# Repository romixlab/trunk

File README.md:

trunk
=====
Just some projects of mine

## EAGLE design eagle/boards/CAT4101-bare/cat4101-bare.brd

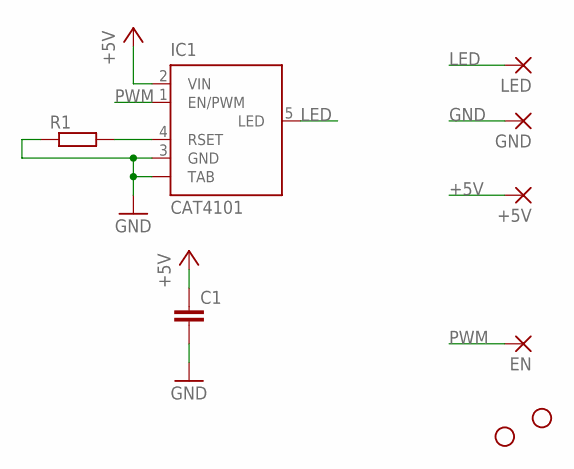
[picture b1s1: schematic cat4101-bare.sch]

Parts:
+5V: SMD2; SMD1,27-2,54
C1: C-EUC0805K; C0805K
EN: SMD2; SMD1,27-2,54
GND: SMD5; SMD2,54-5,08
IC1: CAT4101; TO263_5
JP1, JP2: STAND-OFF
LED: SMD5; SMD2,54-5,08
R1: R-EU_R0805; R0805

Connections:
+5V: +5V.1, C1.1, IC1.2 (VIN)
GND: C1.2, GND.1, IC1.3 (GND), IC1.TAB, R1.1
LED: IC1.5 (LED), LED.1
unnamed: IC1.4 (RSET), R1.2
PWM: EN.1, IC1.1 (EN/PWM)

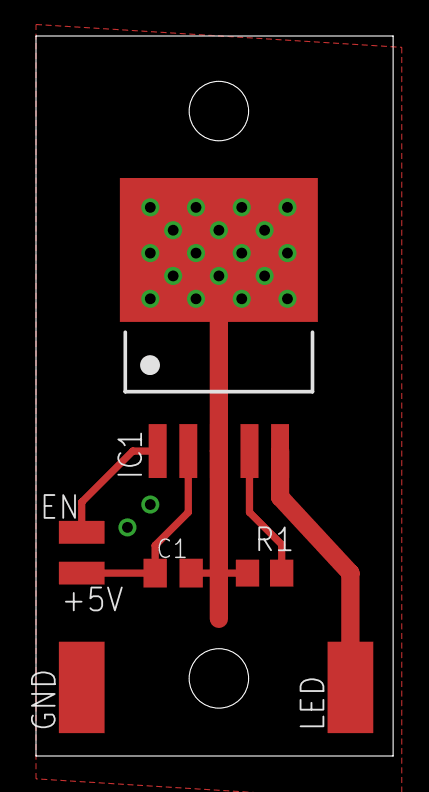
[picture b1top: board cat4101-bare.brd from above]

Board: 2 copper layers, 19.8 x 40.0 mm, 9 parts (0 on the bottom side), 5 nets.

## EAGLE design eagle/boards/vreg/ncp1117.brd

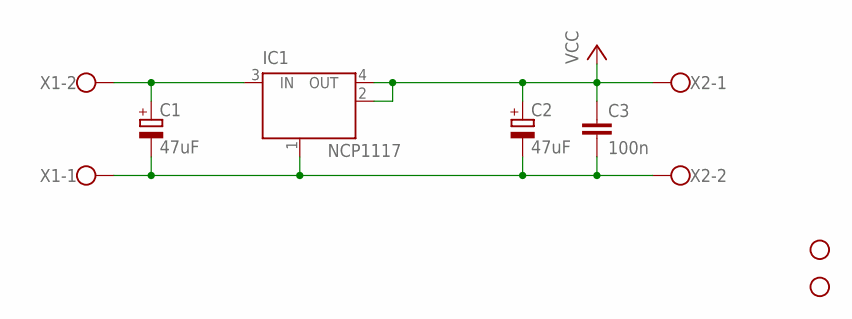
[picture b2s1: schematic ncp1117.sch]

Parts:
C1, C2: 47uF; E2,5-5
C3: 100n; C1206K
IC1: NCP1117; SOT223
STANDOFF1, STANDOFF2: STAND-OFF
X1, X2: W237-102

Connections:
unnamed: C1.+, IC1.3 (IN), X1.2
unnamed: C1.-, C2.-, C3.2, IC1.1 (GND/ADJ), X1.1, X2.2
VCC: C2.+, C3.1, IC1.2 (OUT), IC1.4 (OUT), X2.1

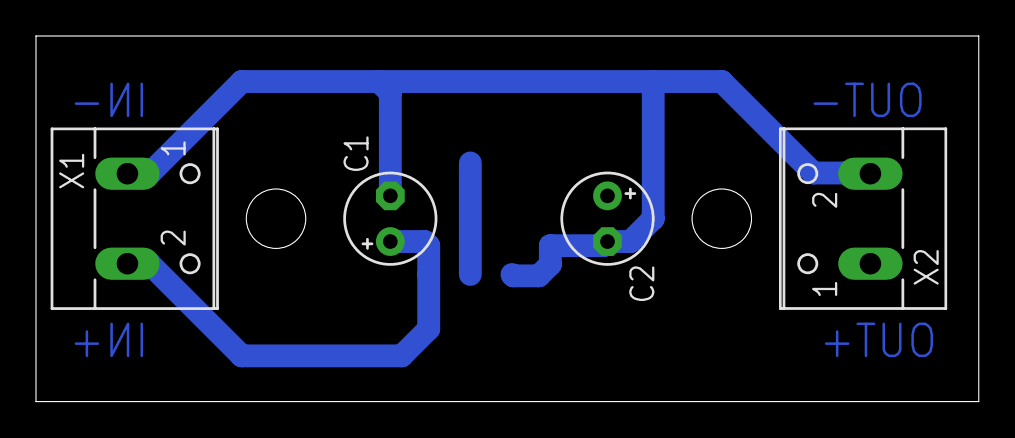
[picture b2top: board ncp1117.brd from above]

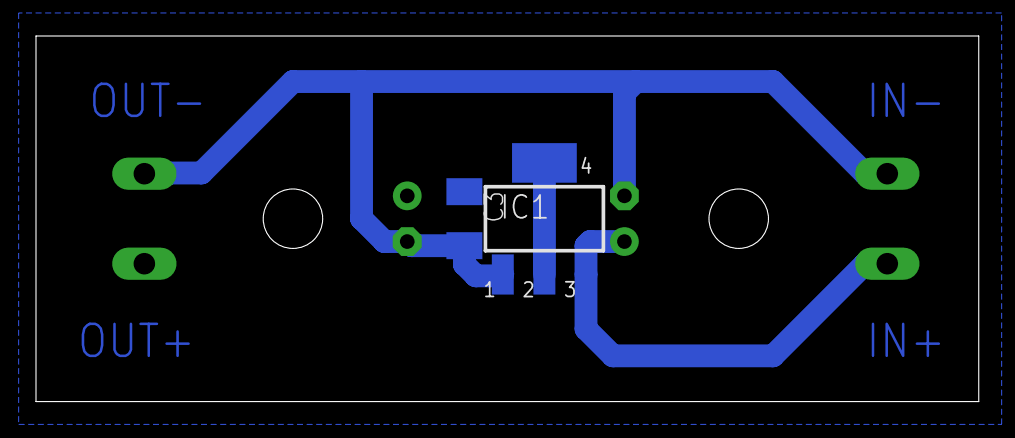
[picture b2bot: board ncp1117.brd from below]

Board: 2 copper layers, 52.4 x 20.3 mm, 8 parts (2 on the bottom side), 3 nets.

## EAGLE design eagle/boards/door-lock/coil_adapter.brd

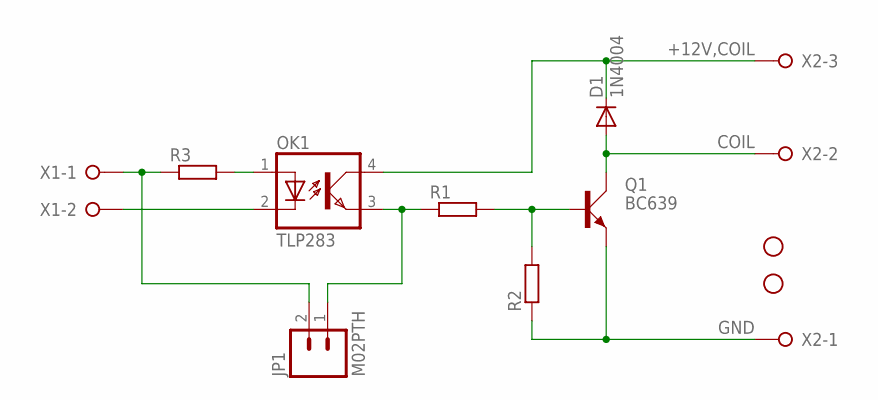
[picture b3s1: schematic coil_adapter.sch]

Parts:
D1: 1N4004; DO41-10
JP1: M02PTH; 1X02
OK1: TLP283; MINI-FLAT-4
Q1: BC639; SOT54D
R1, R2, R3: R-EU_R1206; R1206
STANDOFF1, STANDOFF2: STAND-OFF
X1: W237-02P; W237-132
X2: W237-03P; W237-133

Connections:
+12V,COIL: D1.C, OK1.4 (COL), X2.3
COIL: D1.A, Q1.C, X2.2
GND: Q1.E, R2.1, X2.1
unnamed: Q1.B, R1.2, R2.2
unnamed: JP1.1, OK1.3 (EMIT), R1.1
unnamed: JP1.2, R3.1, X1.1
unnamed: OK1.1 (A), R3.2
unnamed: OK1.2 (C), X1.2

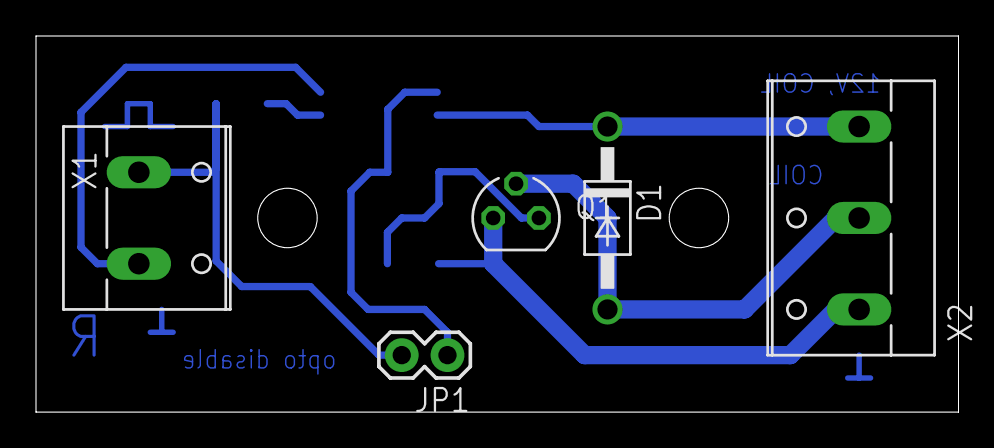
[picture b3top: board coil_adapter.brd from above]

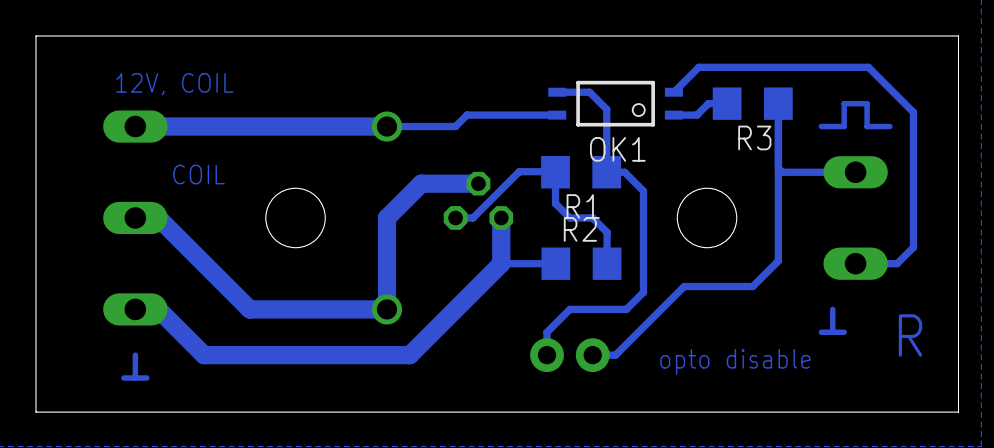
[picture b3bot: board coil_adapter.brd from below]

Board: 2 copper layers, 51.2 x 20.9 mm, 11 parts (4 on the bottom side), 8 nets.

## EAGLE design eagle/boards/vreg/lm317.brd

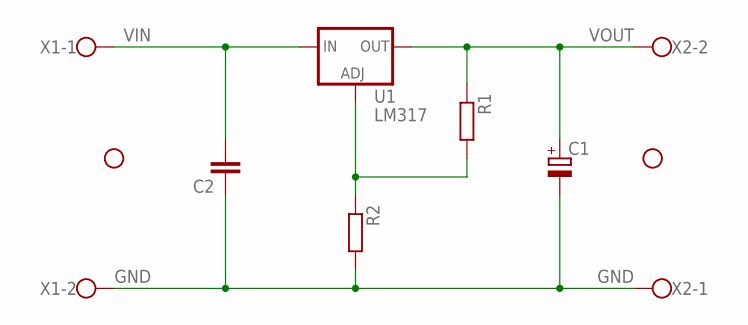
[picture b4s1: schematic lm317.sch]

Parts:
C1: CPOL-EUE2.5-6; E2,5-6
C2: C-EUC1206K; C1206K
R1, R2: R-EU_M1206; M1206
STANDOFF1, STANDOFF2: STAND-OFF
U1: LM317; TO220-ADJ
X1, X2: W237-102

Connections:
GND: C1.-, C2.1, R2.2, X1.2, X2.1
unnamed: R1.2, R2.1, U1.ADJ
VIN: C2.2, U1.IN, X1.1
VOUT: C1.+, R1.1, U1.OUT, X2.2

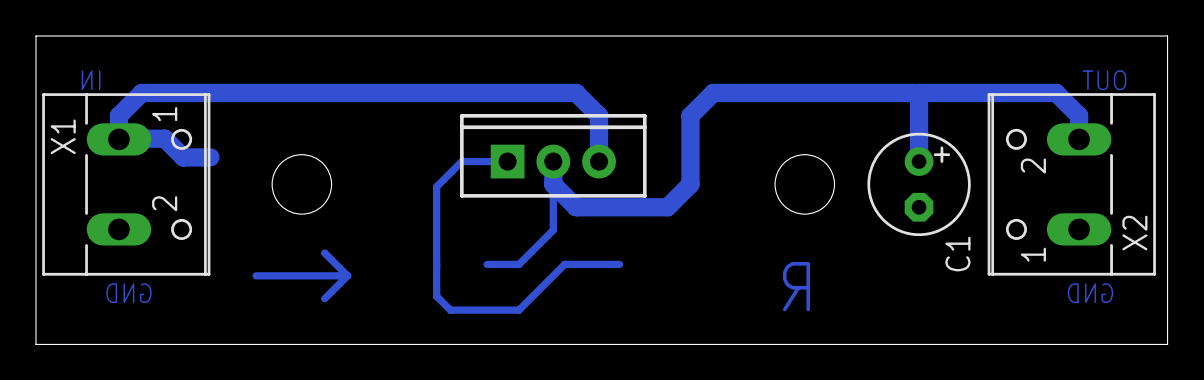
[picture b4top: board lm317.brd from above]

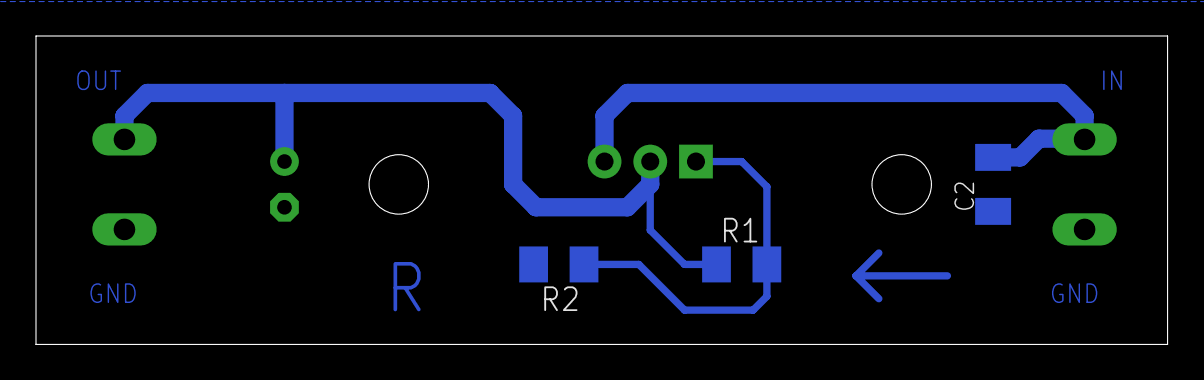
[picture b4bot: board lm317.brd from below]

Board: 2 copper layers, 62.9 x 17.1 mm, 9 parts (3 on the bottom side), 4 nets.

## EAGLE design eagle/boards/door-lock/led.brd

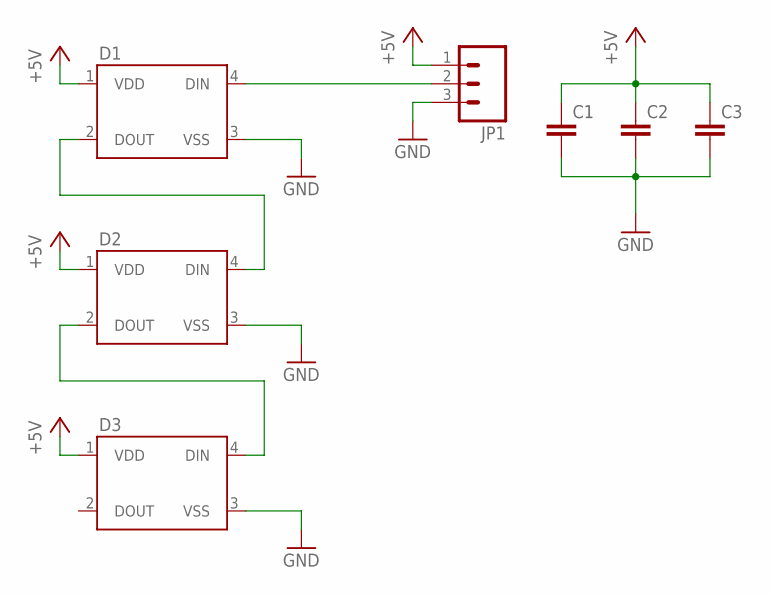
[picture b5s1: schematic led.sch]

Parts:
C1, C2, C3: CAP1206; 1206
D1, D2, D3: WS2812B
JP1: M03PTH; 1X03

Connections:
+5V: C1.1, C2.1, C3.1, D1.1 (VDD), D2.1 (VDD), D3.1 (VDD), JP1.1
GND: C1.2, C2.2, C3.2, D1.3 (VSS), D2.3 (VSS), D3.3 (VSS), JP1.3
unnamed: D1.2 (DOUT), D2.4 (DIN)
unnamed: D2.2 (DOUT), D3.4 (DIN)
unnamed: D1.4 (DIN), JP1.2

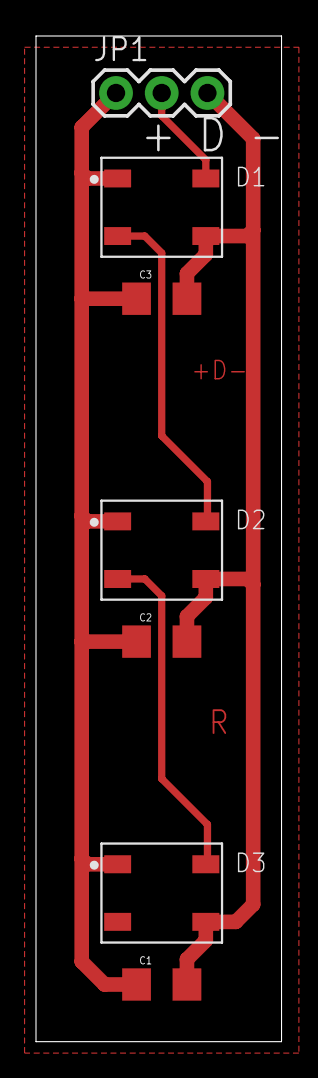
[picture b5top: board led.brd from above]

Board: 2 copper layers, 13.6 x 55.9 mm, 7 parts (0 on the bottom side), 5 nets.

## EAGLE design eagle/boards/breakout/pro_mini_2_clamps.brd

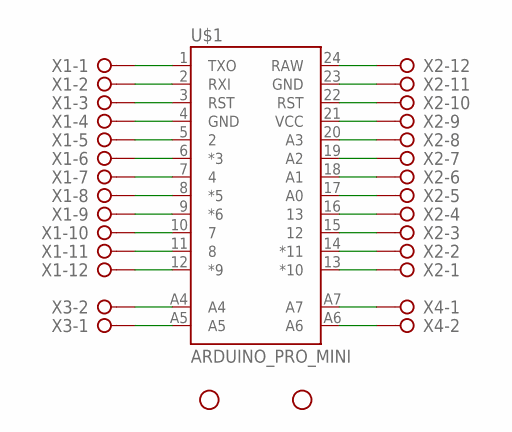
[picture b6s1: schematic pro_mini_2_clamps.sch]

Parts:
STANDOFF1, STANDOFF2: STAND-OFF
U$1: ARDUINO_PRO_MINI
X1, X2: W237-12P
X3, X4: W237-02P; W237-132

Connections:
unnamed: U$1.1 (TXO), X1.1
unnamed: U$1.2 (RXI), X1.2
unnamed: U$1.3 (RST), X1.3
unnamed: U$1.4 (GND), X1.4
unnamed: U$1.5 (2), X1.5
unnamed: U$1.6 (*3), X1.6
unnamed: U$1.7 (4), X1.7
unnamed: U$1.8 (*5), X1.8
unnamed: U$1.9 (*6), X1.9
unnamed: U$1.10 (7), X1.10
unnamed: U$1.11 (8), X1.11
unnamed: U$1.12 (*9), X1.12
unnamed: U$1.24 (RAW), X2.12
unnamed: U$1.23 (GND), X2.11
unnamed: U$1.22 (RST), X2.10
unnamed: U$1.21 (VCC), X2.9
unnamed: U$1.20 (A3), X2.8
unnamed: U$1.19 (A2), X2.7
unnamed: U$1.18 (A1), X2.6
unnamed: U$1.17 (A0), X2.5
unnamed: U$1.16 (13), X2.4
unnamed: U$1.15 (12), X2.3
unnamed: U$1.14 (*11), X2.2
unnamed: U$1.13 (*10), X2.1
unnamed: U$1.A7, X4.1
unnamed: U$1.A6, X4.2
unnamed: U$1.A4, X3.2
unnamed: U$1.A5, X3.1

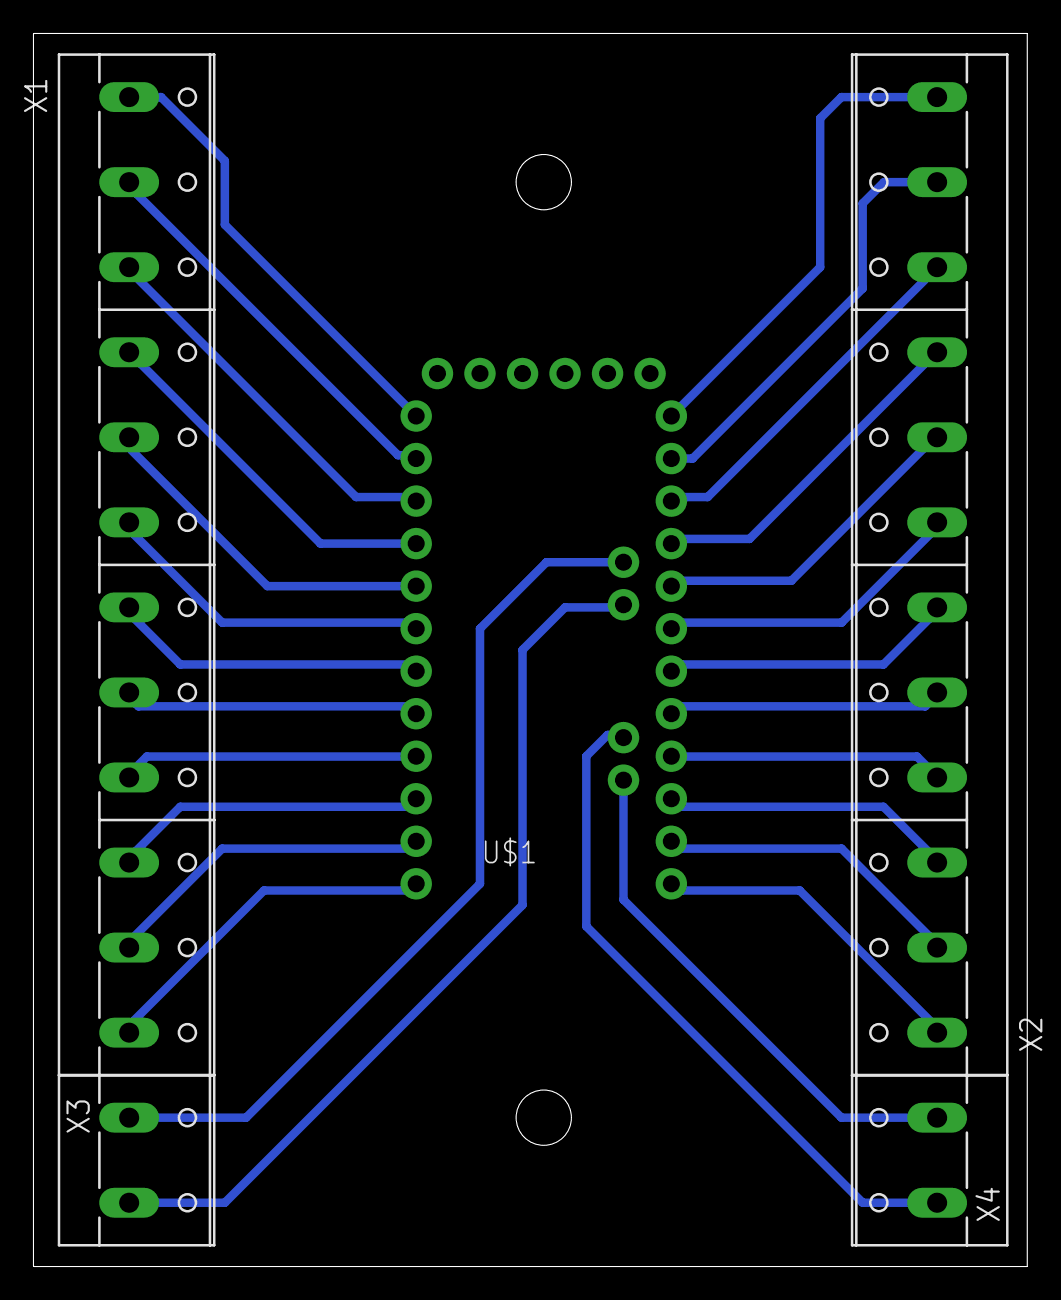
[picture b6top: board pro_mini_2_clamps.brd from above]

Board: 2 copper layers, 59.4 x 73.6 mm, 7 parts (0 on the bottom side), 28 nets.

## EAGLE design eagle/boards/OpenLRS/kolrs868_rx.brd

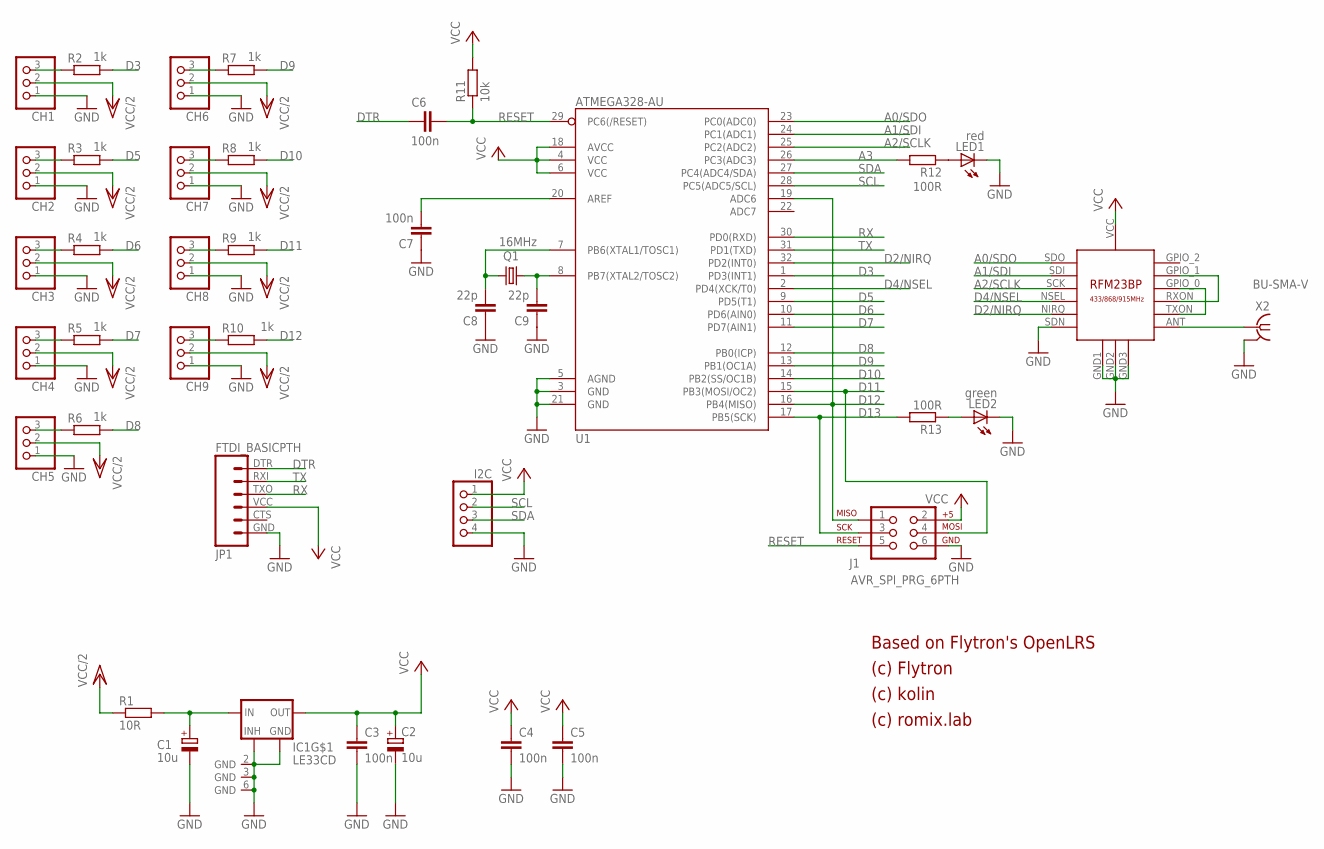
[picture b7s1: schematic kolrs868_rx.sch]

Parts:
C1, C2: 10u; SMC_B
C3, C4, C5, C6, C7: 100n; M0805
C8, C9: 22p; M0805
CH1, CH2, CH3, CH4, CH5, CH6, CH7, CH8, CH9: PINHD-1X3_KOLINOVO; 1X03
I2C: PINHD-1X4; 1X04
IC1: LE33CD; SO8
J1: AVR_SPI_PRG_6PTH; 2X3
JP1: FTDI_BASICPTH; FTDI_BASIC
LED1: red; CHIPLED_0805
LED2: green; CHIPLED_0805
Q1: 16MHz; HC49UP
R1: 10R; M0805
R2, R3, R4, R5, R6, R7, R8, R9, R10: 1k; M0805
R11: 10k; M0805
R12, R13: 100R; M0805
U1: ATMEGA328-AU; TQFP32-08
U$1: RFM23BP
X2: BU-SMA-V

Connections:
A0/SDO: U1.23 (PC0(ADC0)), U$1.SDO
A1/SDI: U1.24 (PC1(ADC1)), U$1.SDI
A2/SCLK: U1.25 (PC2(ADC2)), U$1.SCK
A3: R12.2, U1.26 (PC3(ADC3))
D2/NIRQ: U1.32 (PD2(INT0)), U$1.NIRQ
D3: R2.2, U1.1 (PD3(INT1))
D4/NSEL: U1.2 (PD4(XCK/T0)), U$1.NSEL
D5: R3.2, U1.9 (PD5(T1))
D6: R4.2, U1.10 (PD6(AIN0))
D7: R5.2, U1.11 (PD7(AIN1))
D8: R6.2, U1.12 (PB0(ICP))
D9: R7.2, U1.13 (PB1(OC1A))
D10: R8.2, U1.14 (PB2(SS/OC1B))
D11: J1.4, R9.2, U1.15 (PB3(MOSI/OC2))
D12: J1.1, R10.2, U1.16 (PB4(MISO)), U1.19 (ADC6)
D13: J1.3, R13.2, U1.17 (PB5(SCK))
DTR: C6.1, JP1.DTR (1)
GND: C1.-, C2.-, C3.2, C4.2, C5.2, C7.1, C8.1, C9.1, CH1.1, CH2.1, CH3.1, CH4.1, CH5.1, CH6.1, CH7.1, CH8.1, CH9.1, I2C.4, IC1.2 (GND), IC1.3 (GND), IC1.5 (INHIBIT), IC1.6 (GND), IC1.7 (GND), J1.6, JP1.GND (6), LED1.C, LED2.C, U1.3 (GND), U1.5 (AGND), U1.21 (GND), U$1.GND1, U$1.GND2, U$1.GND3, U$1.SDN, X2.2 (GND), X2.3 (GND), X2.4 (GND), X2.5 (GND)
unnamed: C7.2, U1.20 (AREF)
unnamed: U$1.ANT, X2.1
unnamed: LED1.A, R12.1
unnamed: C8.2, Q1.2, U1.7 (PB6(XTAL1/TOSC1))
unnamed: C9.2, Q1.1, U1.8 (PB7(XTAL2/TOSC2))
unnamed: C1.+, IC1.8 (IN), R1.2
unnamed: CH5.3, R6.1
unnamed: CH1.3, R2.1
unnamed: CH2.3, R3.1
unnamed: CH3.3, R4.1
unnamed: CH4.3, R5.1
unnamed: CH6.3, R7.1
unnamed: CH7.3, R8.1
unnamed: CH8.3, R9.1
unnamed: CH9.3, R10.1
unnamed: U$1.GPIO_0, U$1.TXON
unnamed: U$1.GPIO_1, U$1.RXON
unnamed: LED2.A, R13.1
RESET: C6.2, J1.5, R11.1, U1.29 (PC6(/RESET))
RX: JP1.TXO (3), U1.30 (PD0(RXD))
SCL: I2C.2, U1.28 (PC5(ADC5/SCL))
SDA: I2C.3, U1.27 (PC4(ADC4/SDA))
TX: JP1.RXI (2), U1.31 (PD1(TXD))
VCC: C2.+, C3.1, C4.1, C5.1, I2C.1, IC1.1 (OUT), J1.2, JP1.VCC (4), R11.2, U1.4 (VCC), U1.6 (VCC), U1.18 (AVCC), U$1.VCC
VCC/2: CH1.2, CH2.2, CH3.2, CH4.2, CH5.2, CH6.2, CH7.2, CH8.2, CH9.2, R1.1

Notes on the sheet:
Based on Flytron's OpenLRS
(c) Flytron
(c) kolin
(c) romix.lab

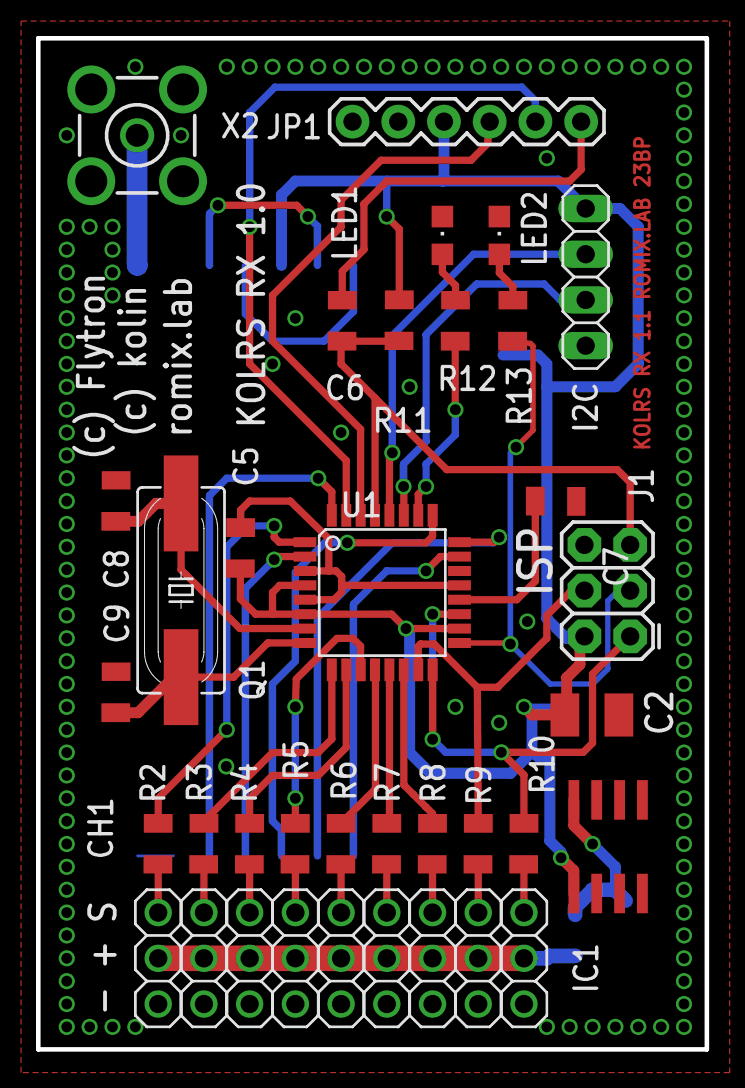
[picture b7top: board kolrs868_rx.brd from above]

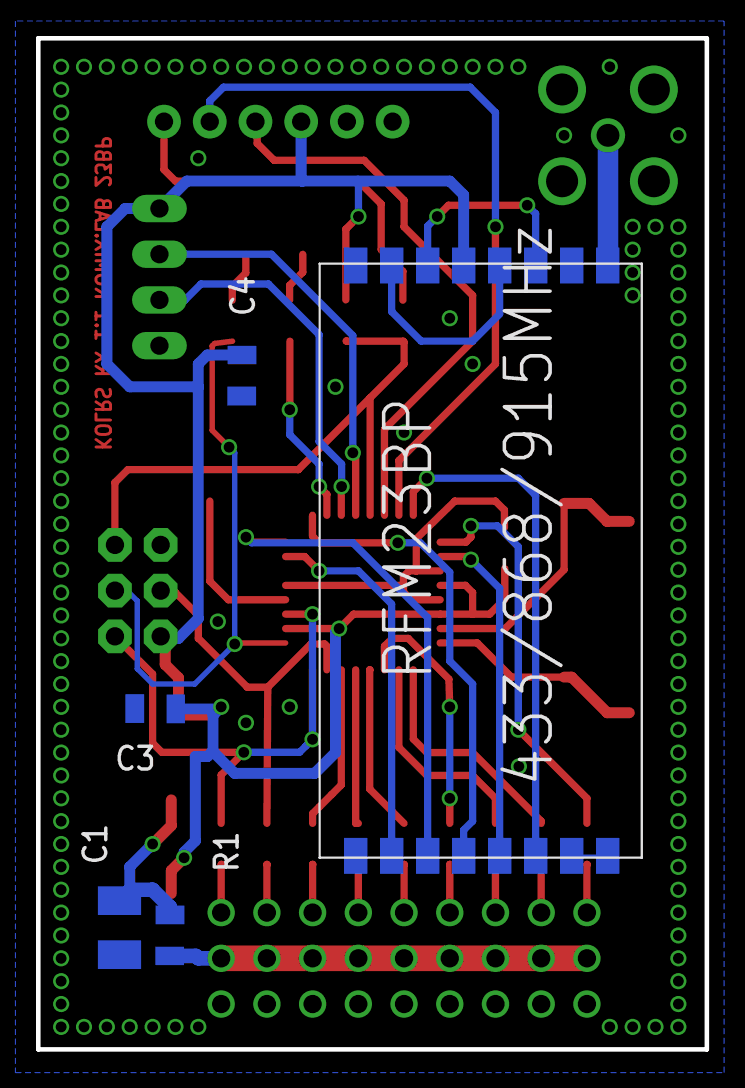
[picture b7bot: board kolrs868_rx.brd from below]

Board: 2 copper layers, 37.1 x 56.2 mm, 41 parts (5 on the bottom side), 43 nets.

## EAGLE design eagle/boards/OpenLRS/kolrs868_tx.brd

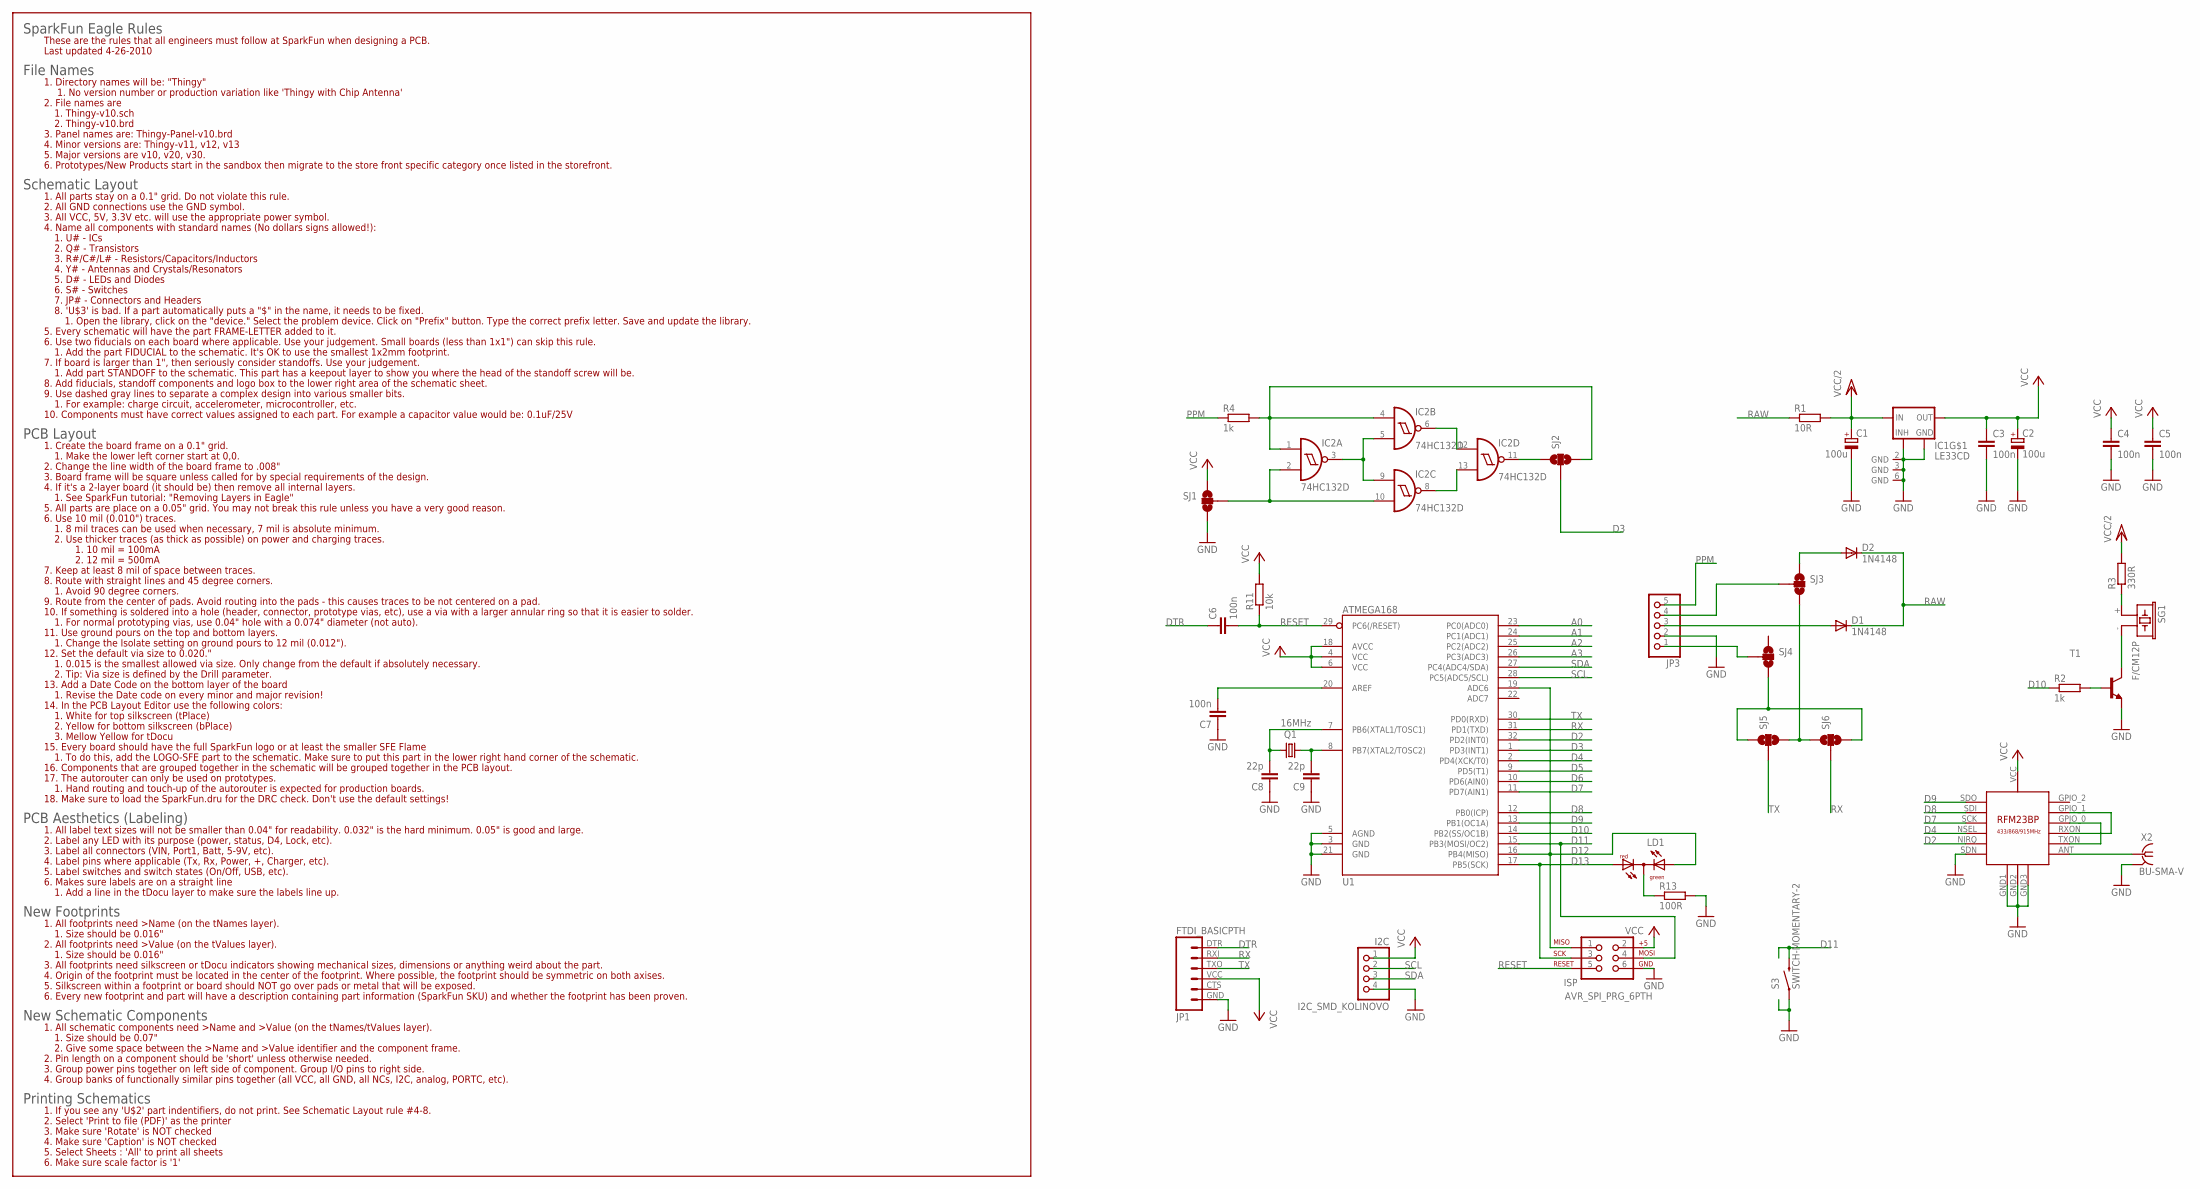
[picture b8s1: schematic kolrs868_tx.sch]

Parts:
C1, C2: 100u; SMC_B
C3, C4, C5, C6, C7: 100n; M0805
C8, C9: 22p; M0805
D1, D2: 1N4148; MINIMELF
I2C: I2C_SMD_KOLINOVO; 1X04
IC1: LE33CD; SO8
IC2: 74HC132D; SO14
ISP: AVR_SPI_PRG_6PTH; 2X3
JP1: FTDI_BASICPTH; FTDI_BASIC
JP3: PINHD-1X5; 1X05
LD1: DUOLED-RG-C; DUOLED-C-5MM
Q1: 16MHz; HC49UP
R1: 10R; M0805
R2, R4: 1k; M0805
R3: 330R; M0805
R11: 10k; M0805
R13: 100R; M0805
S3: SWITCH-MOMENTARY-2; TACTILE_SWITCH_TALL
SG1: F/CM12P
SJ1, SJ2, SJ3, SJ4, SJ5, SJ6: SOLDERJUMPER_2WAYS; SJ_3
T1: BC848-NPN-SOT23-BEC; SOT23-BEC
U1: ATMEGA168; TQFP32-08
U$3: RFM23BP
X2: BU-SMA-V

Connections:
A0: U1.23 (PC0(ADC0))
A1: U1.24 (PC1(ADC1))
A2: U1.25 (PC2(ADC2))
A3: U1.26 (PC3(ADC3))
D2: U1.32 (PD2(INT0)), U$3.NIRQ
D3: SJ2.2, U1.1 (PD3(INT1))
D4: U1.2 (PD4(XCK/T0)), U$3.NSEL
D5: U1.9 (PD5(T1))
D6: U1.10 (PD6(AIN0))
D7: U1.11 (PD7(AIN1)), U$3.SCK
D8: U1.12 (PB0(ICP)), U$3.SDI
D9: U1.13 (PB1(OC1A)), U$3.SDO
D10: R2.1, U1.14 (PB2(SS/OC1B))
D11: ISP.4, S3.B2 (2), U1.15 (PB3(MOSI/OC2))
D12: ISP.1, LD1.AX (AG), U1.16 (PB4(MISO)), U1.19 (ADC6)
D13: ISP.3, LD1.AR, U1.17 (PB5(SCK))
DTR: C6.1, JP1.DTR (1)
GND: C1.-, C2.-, C3.2, C4.2, C5.2, C7.1, C8.1, C9.1, I2C.4, IC1.2 (GND), IC1.3 (GND), IC1.5 (INHIBIT), IC1.6 (GND), IC1.7 (GND), IC2.7 (GND), ISP.6, JP1.GND (6), JP3.2, R13.2, S3.A2 (1), SJ1.3, T1.E, U1.3 (GND), U1.5 (AGND), U1.21 (GND), U$3.GND1, U$3.GND2, U$3.GND3, U$3.SDN, X2.2 (GND), X2.3 (GND), X2.4 (GND), X2.5 (GND)
unnamed: C7.2, U1.20 (AREF)
unnamed: U$3.ANT, X2.1
unnamed: JP3.1, SJ4.2
unnamed: C8.2, Q1.2, U1.7 (PB6(XTAL1/TOSC1))
unnamed: C9.2, Q1.1, U1.8 (PB7(XTAL2/TOSC2))
unnamed: LD1.C, R13.1
unnamed: R2.2, T1.B
unnamed: SG1.- (2), T1.C
unnamed: R3.1, SG1.+ (1)
unnamed: D1.A, JP3.3
unnamed: JP3.4, SJ3.2
unnamed: D2.A, SJ3.1
unnamed: IC2.3 (O), IC2.5 (I1), IC2.9 (I0)
unnamed: IC2.11 (O), SJ2.1
unnamed: IC2.2 (I1), IC2.10 (I1), SJ1.2
unnamed: IC2.8 (O), IC2.13 (I1)
unnamed: IC2.6 (O), IC2.12 (I0)
unnamed: IC2.1 (I0), IC2.4 (I0), R4.2, SJ2.3
unnamed: SJ4.3, SJ5.1, SJ6.3
unnamed: SJ3.3, SJ5.3, SJ6.1
unnamed: U$3.GPIO_0, U$3.TXON
unnamed: U$3.GPIO_1, U$3.RXON
PPM: JP3.5, R4.1
RAW: D1.C, D2.C, R1.1
RESET: C6.2, ISP.5, R11.1, U1.29 (PC6(/RESET))
RX: JP1.RXI (2), SJ6.2, U1.31 (PD1(TXD))
SCL: I2C.2, U1.28 (PC5(ADC5/SCL))
SDA: I2C.3, U1.27 (PC4(ADC4/SDA))
TX: JP1.TXO (3), SJ5.2, U1.30 (PD0(RXD))
VCC: C2.+, C3.1, C4.1, C5.1, I2C.1, IC1.1 (OUT), IC2.14 (VCC), ISP.2, JP1.VCC (4), R11.2, SJ1.1, U1.4 (VCC), U1.6 (VCC), U1.18 (AVCC), U$3.VCC
VCC/2: C1.+, IC1.8 (IN), R1.2, R3.2

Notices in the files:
parts and their libraries:
SparkFun-Boards: Licensing: Creative Commons ShareAlike 4.0 International - https://creativecommons.org/licenses/by-sa/4.0
